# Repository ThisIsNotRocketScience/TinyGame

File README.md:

# TinyGame
A very very small gaming device. 
Based on a Freescale/NXP KL02 microcontroller, a 64x32 pixel black/white OLED display.
Firmware updatable through the audio jack

Soon available on www.thisisnotrocketscience.nl 

Follow our progress on [twitter](https://twitter.com/rocket_not)

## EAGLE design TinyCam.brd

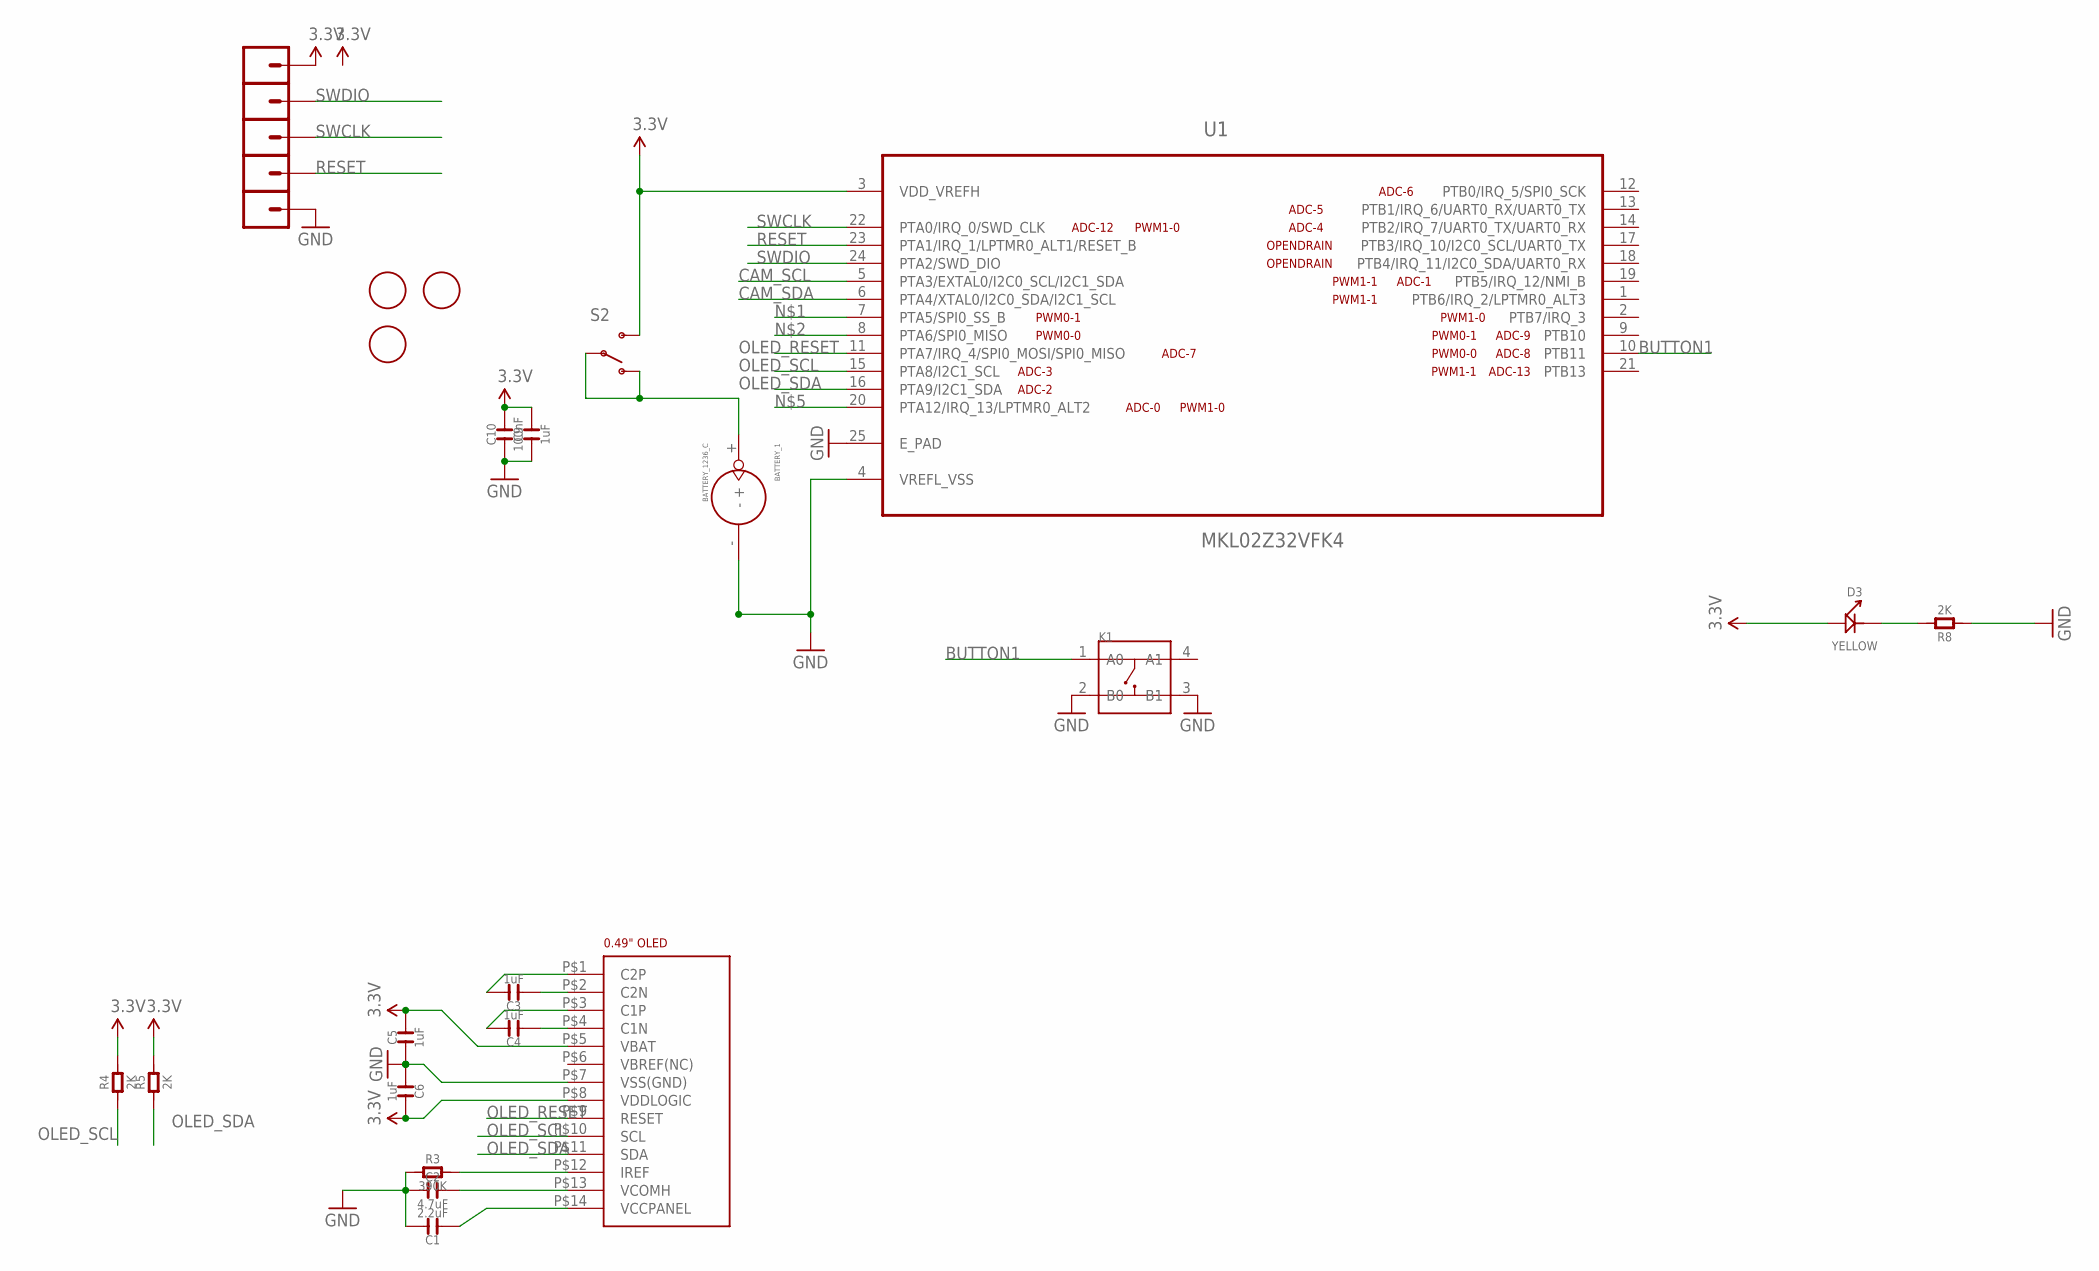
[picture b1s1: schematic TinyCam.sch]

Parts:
BATTERY_1: BATTERY_1236_C
C1: 2.2uF; C0603
C2: 4.7uF; C0603
C3, C4, C5, C6, C9: 1uF; C0603
C10: 100nF; C0603
D3: YELLOW; LED0603
K1: BUTTON-4P-3100010P1; 4P-SMD-6.0X6.0X5.0H
PTA6_MISO1, PTA6_MISO2, PTA6_MISO3, PTA6_MISO4, PTA6_MISO5: M01SMD-4.5X1.5; PAD-1.5X4.5
R3: 390K; R0603
R4, R5, R8: 2K; R0603
S2: SWITCH-SPDT-SMD-A; SWITCH-SPST-SMD-A
U1: MKL02Z32VFK4; QFN50P400X400X100-25N
U$1: 0.49"OLEDFOLDED; 0.49"-FPC-0.7-14-FOLDED
U$2, U$3, U$4: FIDUCIAL; FIDUCIAL_1MM

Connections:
3.3V: C5.2, C6.2, C9.2, C10.2, D3.+, PTA6_MISO1.P$1, R4.2, R5.2, S2.3 (S), U1.3 (VDD_VREFH), U$1.P$5 (VBAT), U$1.P$8 (VDDLOGIC)
BUTTON1: K1.1 (A0), U1.10 (PTB11)
CAM_SCL: U1.5 (PTA3/EXTAL0/I2C0_SCL/I2C1_SDA)
CAM_SDA: U1.6 (PTA4/XTAL0/I2C0_SDA/I2C1_SCL)
GND: BATTERY_1.-, C1.2, C2.1, C5.1, C6.1, C9.1, C10.1, K1.2 (B0), K1.3 (B1), PTA6_MISO5.P$1, R3.1, R8.1, U1.4 (VREFL_VSS), U1.25 (E_PAD), U$1.P$7 (VSS(GND))
unnamed: C3.2, U$1.P$1 (C2P)
unnamed: C4.2, U$1.P$3 (C1P)
unnamed: R3.2, U$1.P$12 (IREF)
unnamed: C1.1, U$1.P$14 (VCCPANEL)
unnamed: C2.2, U$1.P$13 (VCOMH)
unnamed: C3.1, U$1.P$2 (C2N)
unnamed: C4.1, U$1.P$4 (C1N)
unnamed: D3.-, R8.2
OLED_RESET: U1.11 (PTA7/IRQ_4/SPI0_MOSI/SPI0_MISO), U$1.P$9 (RESET)
OLED_SCL: R4.1, U1.15 (PTA8/I2C1_SCL), U$1.P$10 (SCL)
OLED_SDA: R5.1, U1.16 (PTA9/I2C1_SDA), U$1.P$11 (SDA)
RESET: PTA6_MISO4.P$1, U1.23 (PTA1/IRQ_1/LPTMR0_ALT1/RESET_B)
SWCLK: PTA6_MISO3.P$1, U1.22 (PTA0/IRQ_0/SWD_CLK)
SWDIO: PTA6_MISO2.P$1, U1.24 (PTA2/SWD_DIO)
VBAT: BATTERY_1.+, S2.1 (O), S2.2

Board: 2 copper layers, 26 parts (0 on the bottom side), 18 nets, no tracks yet.

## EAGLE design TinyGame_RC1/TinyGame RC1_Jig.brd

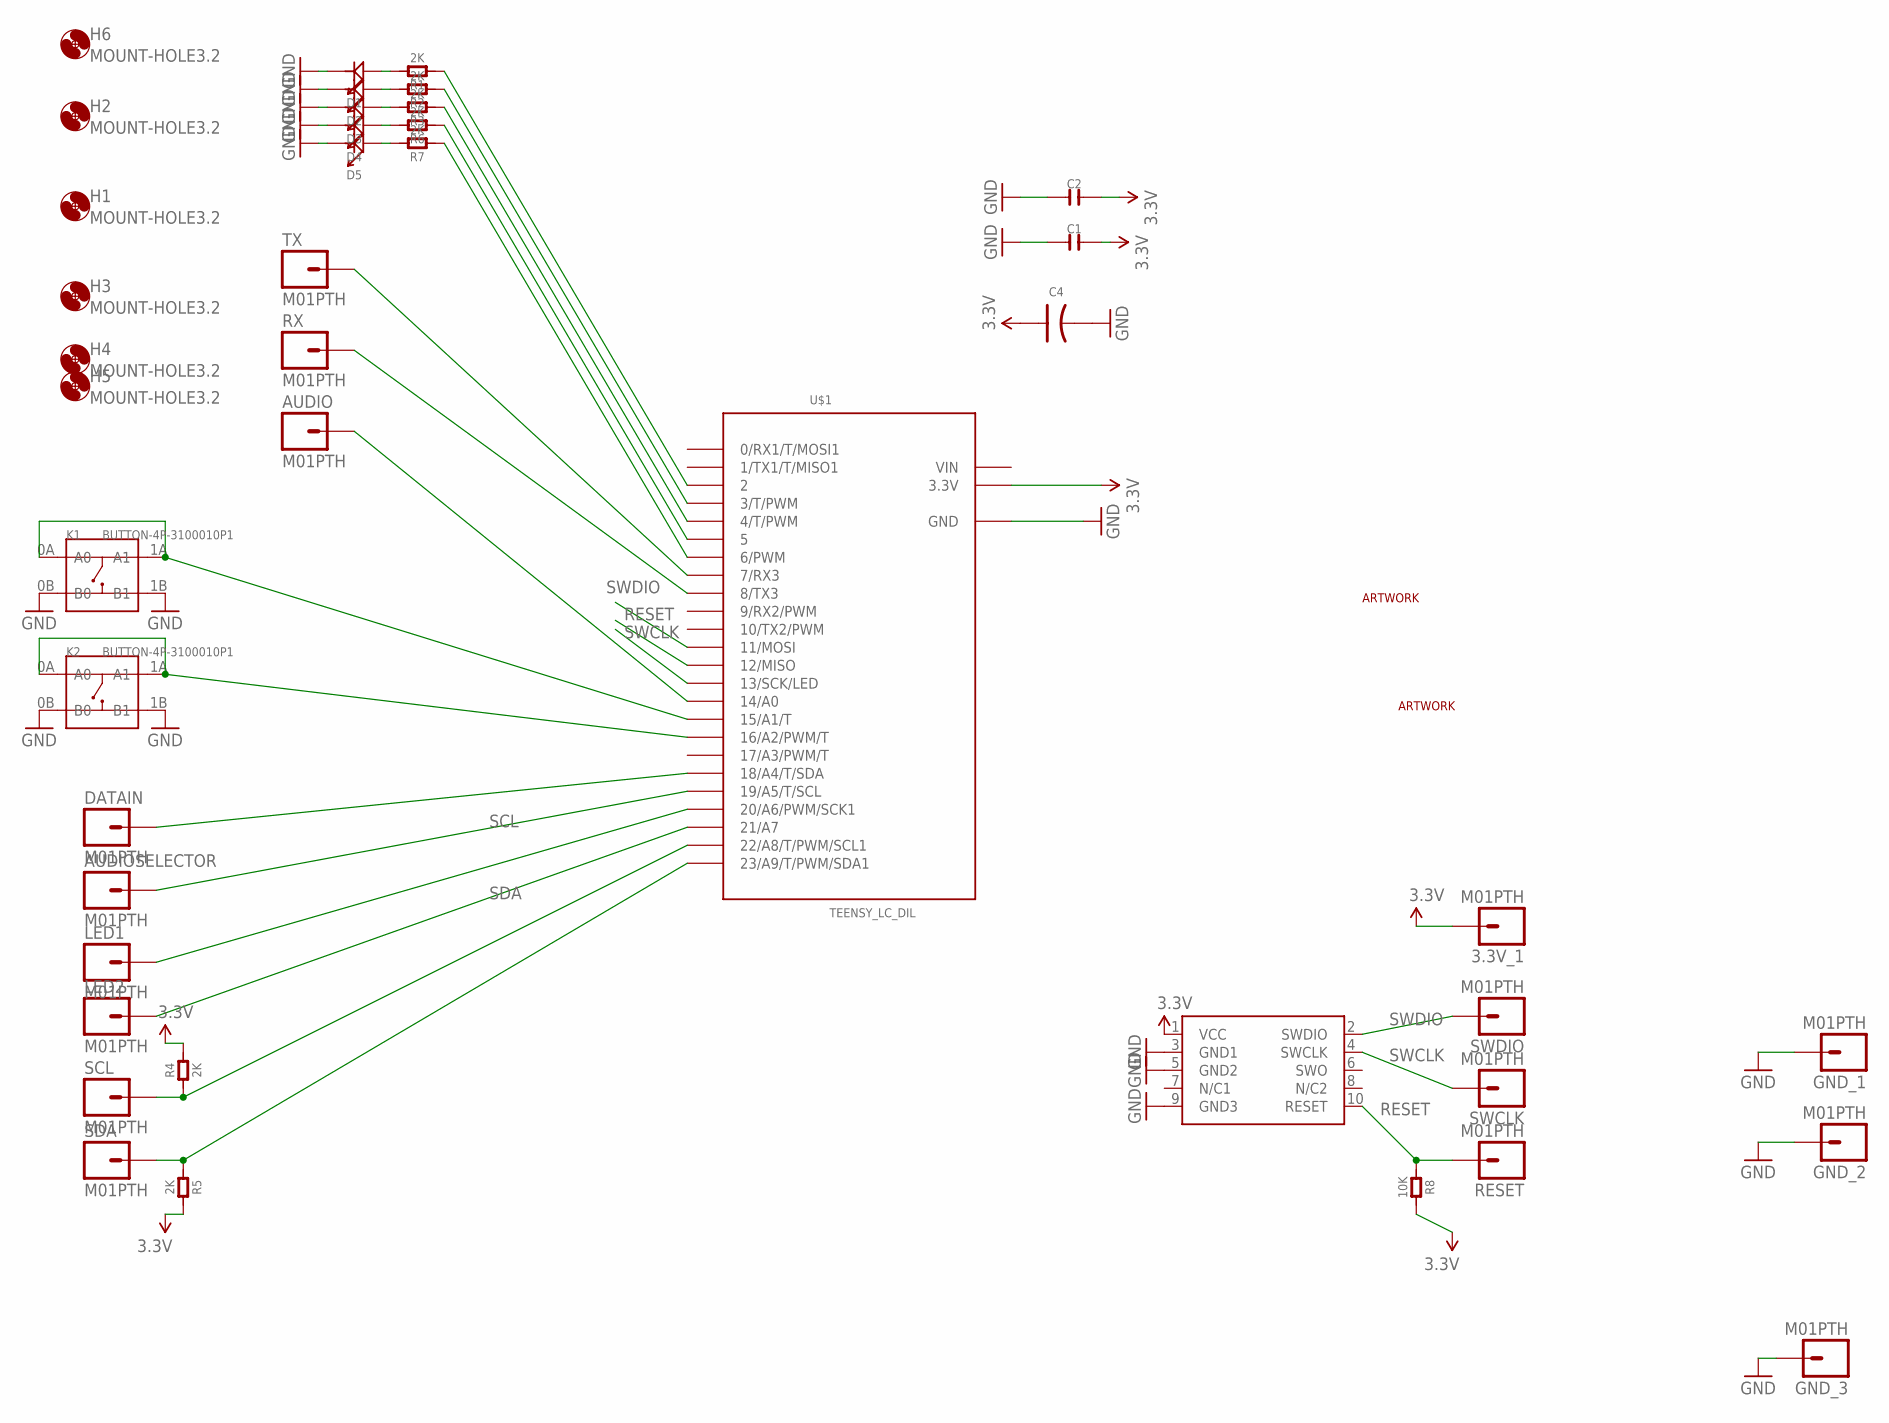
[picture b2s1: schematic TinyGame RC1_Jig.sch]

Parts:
3.3V_1: M01PTH; 1X01
AUDIO: M01PTH; 1X01
AUDIOSELECTOR: M01PTH; 1X01
C1, C2: C-0603; C0603
C4: C-POLAR-A; AVX-A
D1, D2, D3, D4, D5: LED; LED0603
DATAIN: M01PTH; 1X01
GND_1, GND_2, GND_3: M01PTH; 1X01
H1, H2, H3, H4, H5, H6: MOUNT-HOLE3.2; 3,2
K1, K2: BUTTON-4P-3100010P1; 4P-SMD-6.0X6.0X5.0H
LED1, LED2: M01PTH; 1X01
R1, R2, R3, R4, R5, R6, R7: 2K; R0603
R8: 10K; R0603
RESET: M01PTH; 1X01
RX: M01PTH; 1X01
SCL: M01PTH; 1X01
SDA: M01PTH; 1X01
SWCLK: M01PTH; 1X01
SWD1: CORTEX_SWDVERT; SWD_VERTICAL
SWDIO: M01PTH; 1X01
TX: M01PTH; 1X01
U$1: TEENSY_LC_DIL; TEENSY_3.0-3.2&LC_DIL
U$2: TINRS_ARTWORKLOGO; TINRSLOGO
U$3: TINRS_ARTWORKROCKET; TINRS_ROCKET

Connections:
3.3V: 3.3V_1.1, C1.2, C2.2, C4.+ (1), R4.2, R5.2, R8.2, SWD1.1 (VCC), U$1.3.3V
GND: C1.1, C2.1, C4.- (2), D1.-, D2.-, D3.-, D4.-, D5.-, GND_1.1, GND_2.1, GND_3.1, K1.0B (B0), K1.1B (B1), K2.0B (B0), K2.1B (B1), SWD1.3 (GND1), SWD1.5 (GND2), SWD1.9 (GND3), U$1.AGND (GND), U$1.GND
unnamed: TX.1, U$1.7 (7/RX3)
unnamed: RX.1, U$1.8 (8/TX3)
unnamed: AUDIO.1, U$1.14/A0
unnamed: LED2.1, U$1.21/A7
unnamed: LED1.1, U$1.20/A6 (20/A6/PWM/SCK1)
unnamed: AUDIOSELECTOR.1, U$1.19/A5 (19/A5/T/SCL)
unnamed: DATAIN.1, U$1.18/A4 (18/A4/T/SDA)
unnamed: R1.1, U$1.2
unnamed: R2.1, U$1.3 (3/T/PWM)
unnamed: R3.1, U$1.4 (4/T/PWM)
unnamed: R6.1, U$1.5
unnamed: R7.1, U$1.6 (6/PWM)
unnamed: D1.+, R1.2
unnamed: D2.+, R2.2
unnamed: D3.+, R3.2
unnamed: D4.+, R6.2
unnamed: D5.+, R7.2
unnamed: K1.0A (A0), K1.1A (A1), U$1.15/A1 (15/A1/T)
unnamed: K2.0A (A0), K2.1A (A1), U$1.16/A2 (16/A2/PWM/T)
RESET: R8.1, RESET.1, SWD1.10 (RESET), U$1.12 (12/MISO)
SCL: R4.1, SCL.1, U$1.22/A8 (22/A8/T/PWM/SCL1)
SDA: R5.1, SDA.1, U$1.23/A9 (23/A9/T/PWM/SDA1)
SWCLK: SWCLK.1, SWD1.4 (SWCLK), U$1.13 (13/SCK/LED)
SWDIO: SWD1.2 (SWDIO), SWDIO.1, U$1.11 (11/MOSI)
VIN: U$1.VIN

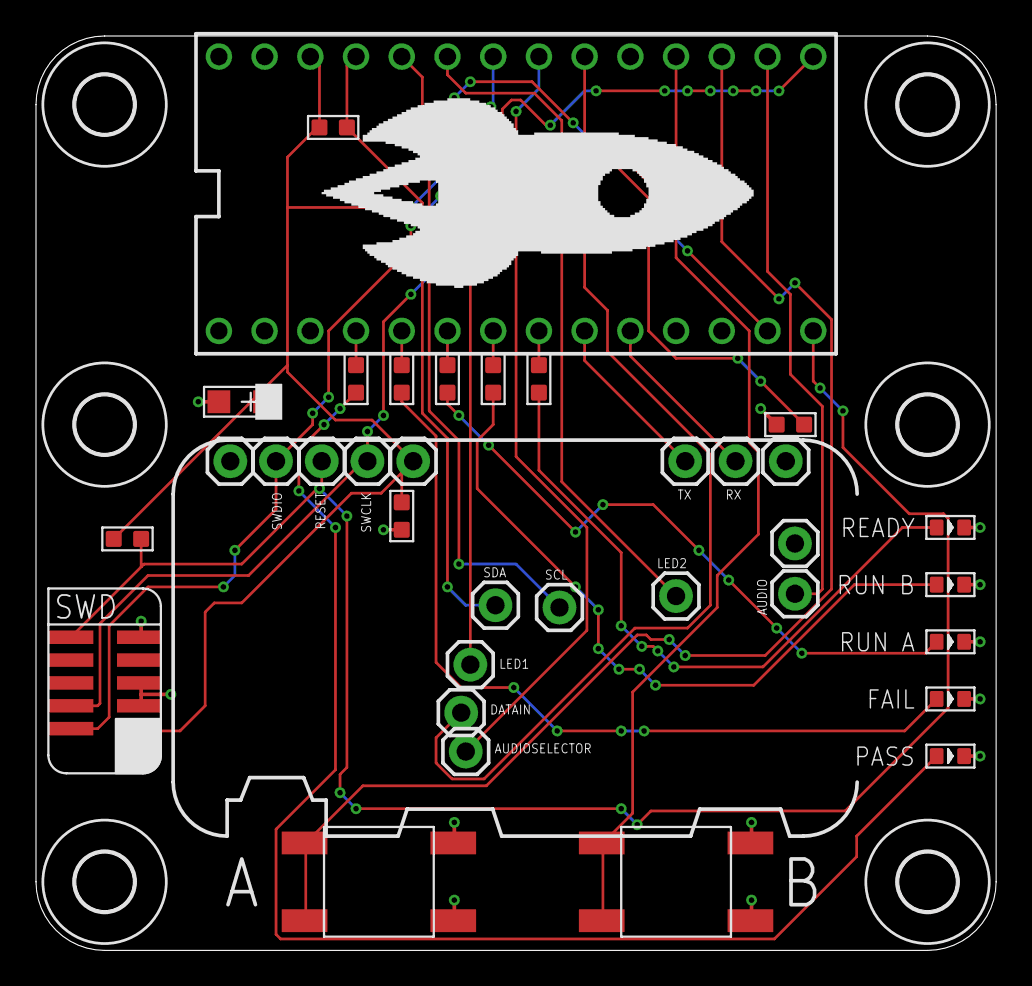
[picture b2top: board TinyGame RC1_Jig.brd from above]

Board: 2 copper layers, 53.3 x 50.8 mm, 44 parts (1 on the bottom side), 26 nets.

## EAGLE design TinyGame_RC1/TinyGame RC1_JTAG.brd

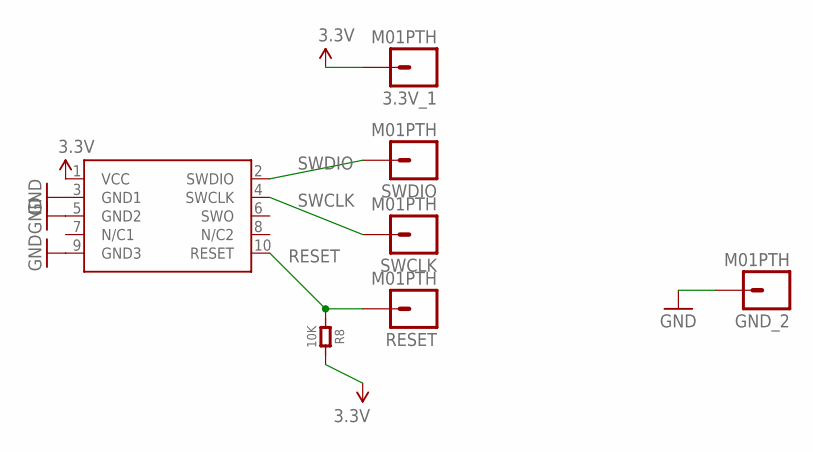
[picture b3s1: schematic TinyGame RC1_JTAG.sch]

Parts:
3.3V_1: M01PTH; 1X01
GND_2: M01PTH; 1X01
R8: 10K; R0603
RESET: M01PTH; 1X01
SWCLK: M01PTH; 1X01
SWD1: CORTEX_SWDVERT; SWD_VERTICAL
SWDIO: M01PTH; 1X01

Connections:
3.3V: 3.3V_1.1, R8.2, SWD1.1 (VCC)
GND: GND_2.1, SWD1.3 (GND1), SWD1.5 (GND2), SWD1.9 (GND3)
RESET: R8.1, RESET.1, SWD1.10 (RESET)
SWCLK: SWCLK.1, SWD1.4 (SWCLK)
SWDIO: SWD1.2 (SWDIO), SWDIO.1

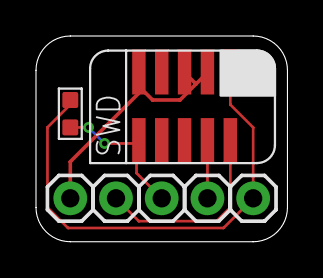
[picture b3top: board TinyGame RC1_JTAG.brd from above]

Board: 2 copper layers, 14.0 x 11.4 mm, 7 parts (0 on the bottom side), 5 nets.

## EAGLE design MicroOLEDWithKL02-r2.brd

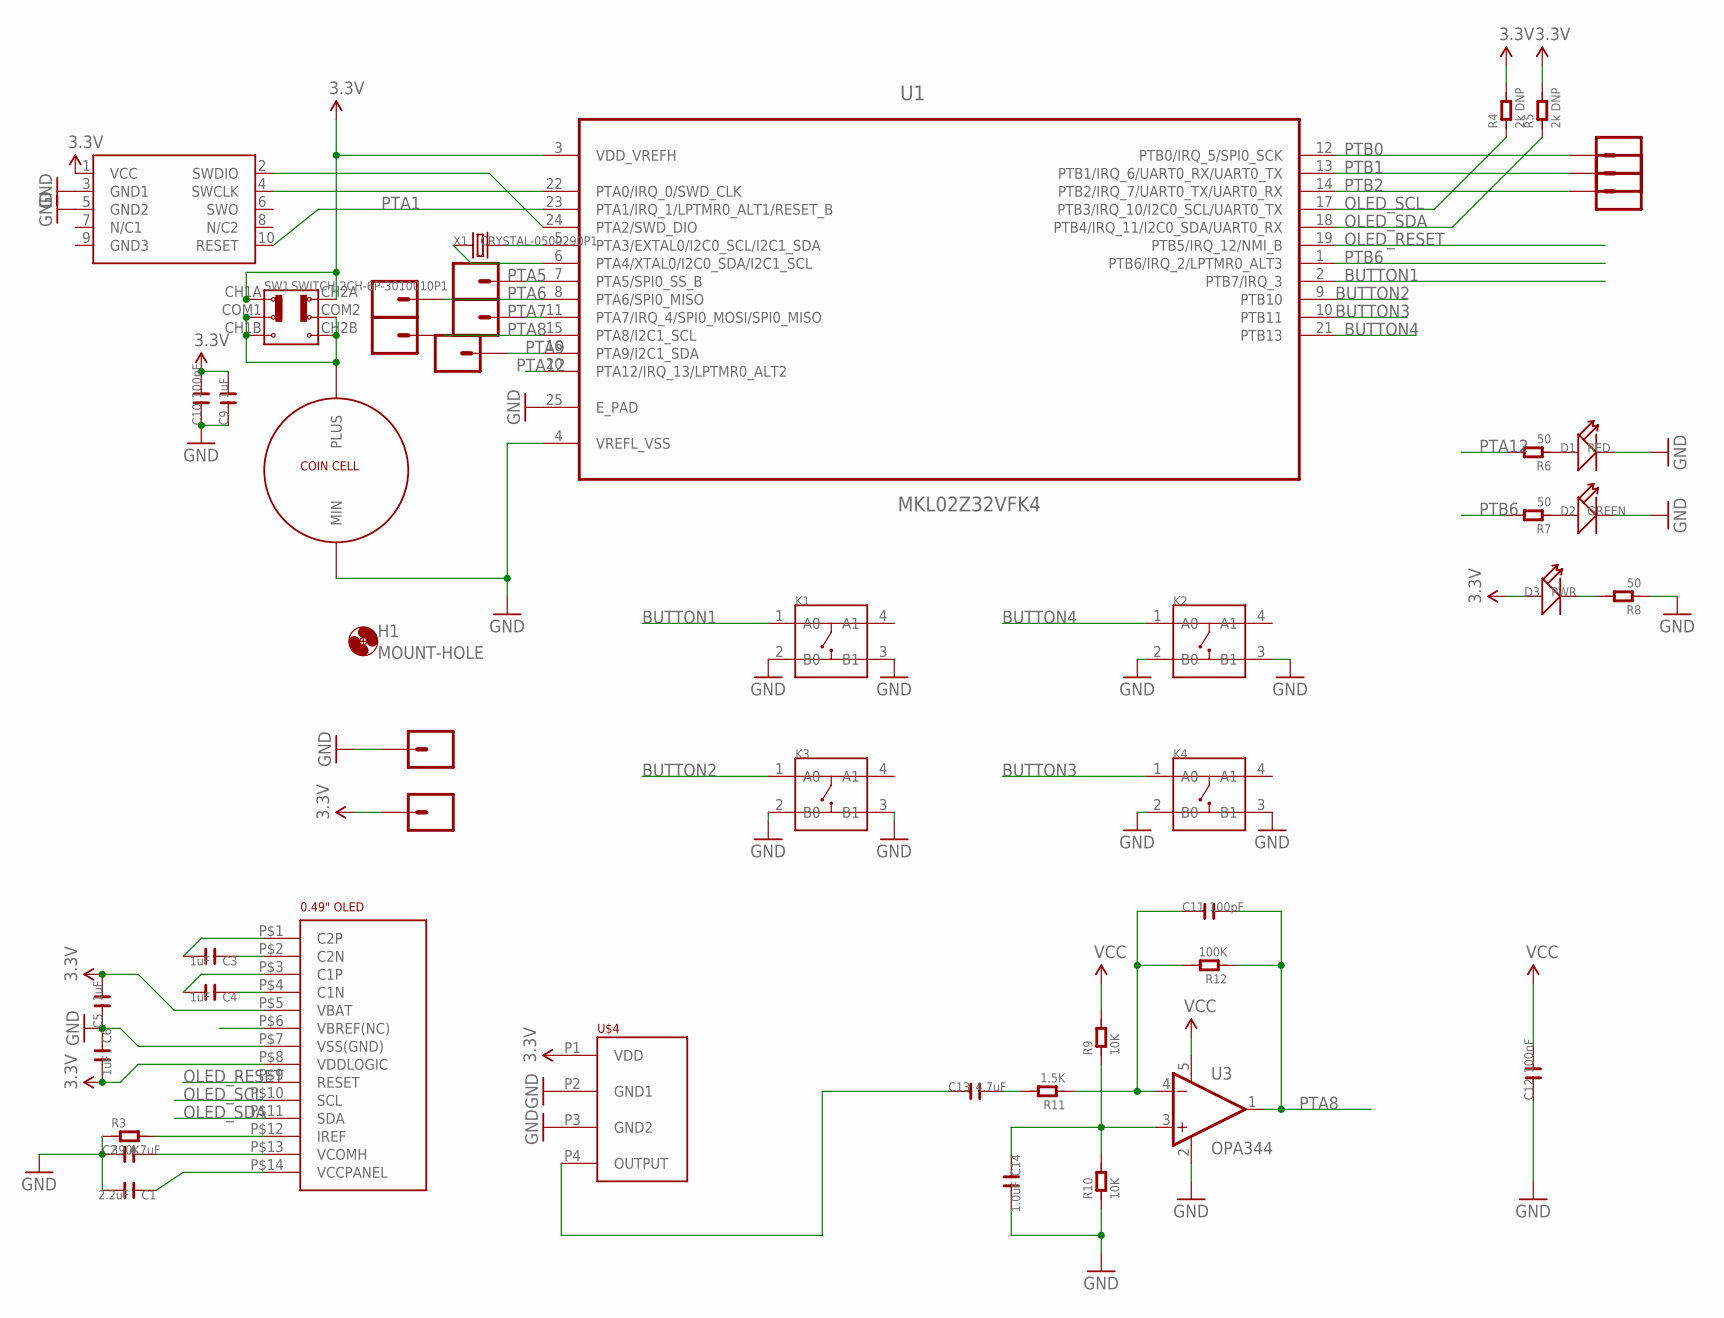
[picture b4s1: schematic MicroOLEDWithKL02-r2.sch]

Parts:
C1: 2.2uF; C0603
C2, C13: 4.7uF; C0603
C3, C4, C5, C6, C9: 1uF; C0603
C10, C12: 100nF; C0603
C11: 100pF; C0603
C14: 1.0uF; C0603
D1: RED; LED0603
D2: GREEN; LED0603
D3: PWR; LED0603
H1: MOUNT-HOLE; 3.2-NOMARKINGS-SMALLSAFEZONE
K1, K2, K3, K4: BUTTON-4P-3100010P1; 4P-SMD-6.0X6.0X5.0H
PTA5_SS, PTA6_MISO, PTA7_MOSI_MISO, PTA8_I2C1_SCL, PTA9_I2C1_SDA: M01SMD-4.5X1.5; PAD-1.5X4.5
PTB0_SCK, PTB1_RXTX, PTB2_TXRX, PTB2_TXRX1, PTB2_TXRX2: M01SMD-4.5X1.5; PAD-1.5X4.5
R3: 390K; R0603
R4, R5: 2k DNP; R0603
R6, R7, R8: 50; R0603
R9, R10: 10K; R0603
R11: 1.5K; R0603
R12: 100K; R0603
SW1: SWITCH-2CH-6P-3010010P1; 6P-2CH-2.54-9.1X3.5X3.2+2H
SWD1: CORTEX_SWD; M50-3600542
U1: MKL02Z32VFK4; QFN50P400X400X100-25N
U3: OPA344; SOT23-5
U$1: 0.49"OLED; FPC-0.7-14
U$4: WM7120A; LGAMS4
U$5: COINCELL; 2032HOLDER-SZ
X1: CRYSTAL-0500290P1; 2P-SMD-5.0X3.2

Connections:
3.3V: C5.2, C6.2, C9.2, C10.2, C12.2, D3.+, PTB2_TXRX1.P$1, R4.2, R5.2, R9.2, SW1.CH1A, SW1.CH2A, SWD1.1 (VCC), U1.3 (VDD_VREFH), U3.5 (V+), U$1.P$5 (VBAT), U$1.P$8 (VDDLOGIC), U$4.P1 (VDD)
BUTTON1: K1.1 (A0), U1.2 (PTB7/IRQ_3)
BUTTON2: K3.1 (A0), U1.9 (PTB10)
BUTTON3: K4.1 (A0), U1.10 (PTB11)
BUTTON4: K2.1 (A0), U1.21 (PTB13)
GND: C1.2, C2.1, C5.1, C6.1, C9.1, C10.1, C12.1, C14.2, D1.-, D2.-, K1.2 (B0), K1.3 (B1), K2.2 (B0), K2.3 (B1), K3.2 (B0), K3.3 (B1), K4.2 (B0), K4.3 (B1), PTB2_TXRX2.P$1, R3.1, R8.1, R10.1, SWD1.3 (GND1), SWD1.5 (GND2), U1.4 (VREFL_VSS), U1.25 (E_PAD), U3.2 (V-), U$1.P$7 (VSS(GND)), U$4.P2 (GND1), U$4.P3 (GND2), U$5.MIN
unnamed: U1.5 (PTA3/EXTAL0/I2C0_SCL/I2C1_SDA), X1.2
unnamed: U1.6 (PTA4/XTAL0/I2C0_SDA/I2C1_SCL), X1.1
unnamed: C3.2, U$1.P$1 (C2P)
unnamed: C4.2, U$1.P$3 (C1P)
unnamed: SWD1.4 (SWCLK), U1.22 (PTA0/IRQ_0/SWD_CLK)
unnamed: D1.+, R6.1
unnamed: SWD1.2 (SWDIO), U1.24 (PTA2/SWD_DIO)
unnamed: R3.2, U$1.P$12 (IREF)
unnamed: C1.1, U$1.P$14 (VCCPANEL)
unnamed: C2.2, U$1.P$13 (VCOMH)
unnamed: C3.1, U$1.P$2 (C2N)
unnamed: C4.1, U$1.P$4 (C1N)
unnamed: D2.+, R7.1
unnamed: C13.1, U$4.P4 (OUTPUT)
unnamed: C11.1, R11.1, R12.2, U3.4 (-IN)
unnamed: C13.2, R11.2
unnamed: C14.1, R9.1, R10.2, U3.3 (+IN)
unnamed: D3.-, R8.2
unnamed: SW1.CH1B, SW1.CH2B, SW1.COM1, SW1.COM2, U$5.PLUS
OLED_RESET: U1.19 (PTB5/IRQ_12/NMI_B), U$1.P$9 (RESET)
OLED_SCL: R4.1, U1.17 (PTB3/IRQ_10/I2C0_SCL/UART0_TX), U$1.P$10 (SCL)
OLED_SDA: R5.1, U1.18 (PTB4/IRQ_11/I2C0_SDA/UART0_RX), U$1.P$11 (SDA)
PTA1: SWD1.10 (RESET), U1.23 (PTA1/IRQ_1/LPTMR0_ALT1/RESET_B)
PTA5: PTA5_SS.P$1, U1.7 (PTA5/SPI0_SS_B)
PTA6: PTA6_MISO.P$1, U1.8 (PTA6/SPI0_MISO)
PTA7: PTA7_MOSI_MISO.P$1, U1.11 (PTA7/IRQ_4/SPI0_MOSI/SPI0_MISO)
PTA8: C11.2, PTA8_I2C1_SCL.P$1, R12.1, U1.15 (PTA8/I2C1_SCL), U3.1 (OUT)
PTA9: PTA9_I2C1_SDA.P$1, U1.16 (PTA9/I2C1_SDA)
PTA12: R6.2, U1.20 (PTA12/IRQ_13/LPTMR0_ALT2)
PTB0: PTB0_SCK.P$1, U1.12 (PTB0/IRQ_5/SPI0_SCK)
PTB1: PTB1_RXTX.P$1, U1.13 (PTB1/IRQ_6/UART0_RX/UART0_TX)
PTB2: PTB2_TXRX.P$1, U1.14 (PTB2/IRQ_7/UART0_TX/UART0_RX)
PTB6: R7.2, U1.1 (PTB6/IRQ_2/LPTMR0_ALT3)

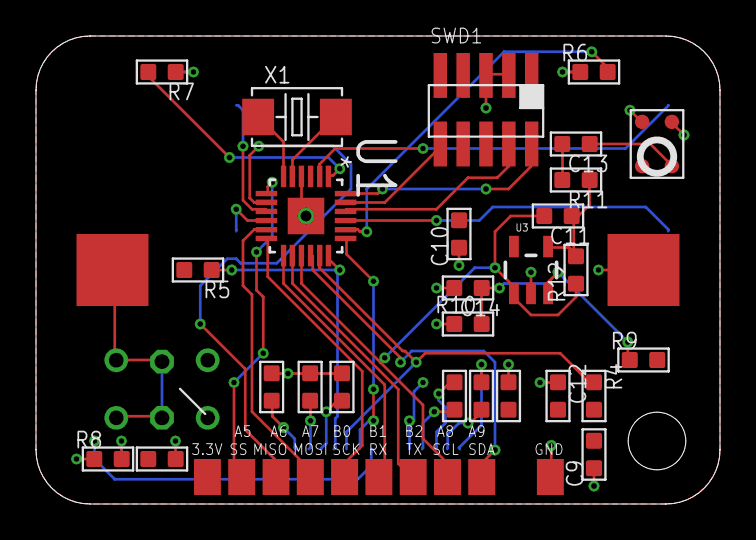
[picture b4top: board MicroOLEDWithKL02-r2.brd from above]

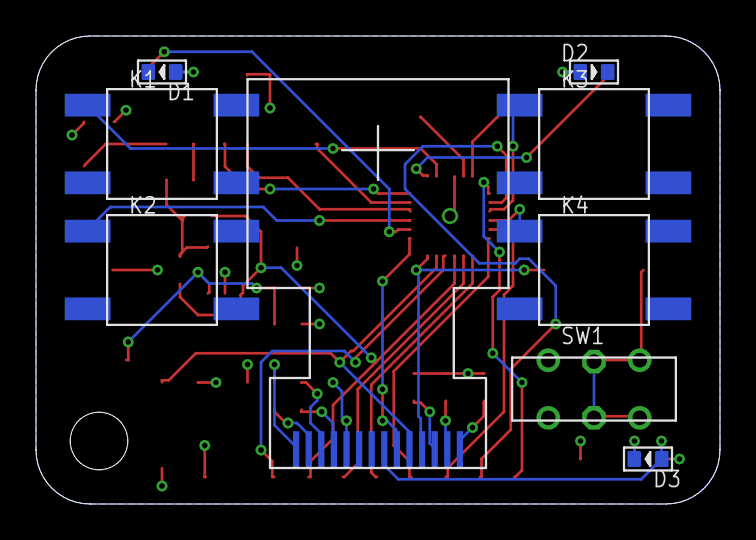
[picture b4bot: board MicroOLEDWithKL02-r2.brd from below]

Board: 2 copper layers, 38.0 x 26.0 mm, 48 parts (9 on the bottom side), 39 nets.

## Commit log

2015-11-25 Boards committed..
2016-11-12 Added TinyGame RC1 to the repo
2016-11-15 Audioboot progress
2016-11-16 Moved some stuff around - added testjig and jtag adapter
2016-11-28 Many Tiny Updates
2016-11-30 RC2 design update for programming
2016-12-02 TinyGame ArtUpdate
2016-12-03 Artwork and gerbers
2016-12-25 Bitman!
2017-01-04 TinyGame boot system progress
2017-01-04 Loader updates - bootscreen, progressbar, artwork
2017-01-04 Missing files
2017-01-04 Bootloader progress - WAVEROCKET
2017-07-01 Audio in bitman!

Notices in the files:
parts and their libraries:
SparkFun-Connectors: Licensing: CC v3.0 Share-Alike You are welcome to use this library for commercial purposes.
